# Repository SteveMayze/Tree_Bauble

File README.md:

# Tree_Bauble

## Basic Design
The Tree Bauble is simply a Christmas tree ornament that will contain some blinking LEDs. 
The concept of the design is to take a clear plastic ornament and build into this a main 
board with six arcs of flexible boards that would contain the LEDs.

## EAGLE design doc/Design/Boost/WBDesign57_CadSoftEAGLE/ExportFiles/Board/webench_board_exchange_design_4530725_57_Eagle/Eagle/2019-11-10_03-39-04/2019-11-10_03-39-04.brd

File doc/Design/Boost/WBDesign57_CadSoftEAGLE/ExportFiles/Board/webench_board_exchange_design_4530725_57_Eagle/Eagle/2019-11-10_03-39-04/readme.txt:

**********************************************************
*************  Important Instructions Follow  ************
**********************************************************
 
All files exported to: Z:\\45\\30\\4530725\\57\Eagle\2019-11-10_03-39-04\2019-11-10_03-39-04.xml

**********************************************************
*****************Schematic Instructions  *******************
**********************************************************

To import your new Schematic file into Eagle:

1. Unzip the downloaded folder files to local directory and Start Eagle.
2. Select "File"->"Open"->"Schematic..." from the menu at the top of
the screen.
3. Browse to your newly exported file and select the ".sch" file extension.
4. You should now see your schamtic available in Eagle.

**********************************************************
*******************  PCB Instructions  *******************
**********************************************************

To import your new BOARD file into Eagle:

1. Unzip the downloaded folder files to local directory and Start Eagle.
2. Select "File"->"Open"->"Board..." from the menu at the top of
the screen.
3. Browse to your newly exported file and select the ".brd" file extension.
4. Planes will need to be repoured to update the polygon fills
	1. Once your board is loaded, type "ratsnest" into the command
	   line and press the Enter key.
	2. The polygons should all be filled now.
5. You should now have an image of your board available in Eagle.

**********************************************************
*******************  LIB Instructions  *******************
**********************************************************

To import your new library into Eagle:

1. Start Eagle.
2. Select "File"->"New"->"Library" from the menu.
3. In the blank library window, select "File" -> "Execute Script"
from the menu.
5. Browse to your newly exported Eagle Script file (".scr" file extension)
6. After opening the file, the script will populate the new library.
Layer 93 should NOT exist.
7. Use "File"->Save As: "AcceleratedDesigns_Lib.lbr" and to the desired
location in Eagle native format.
8. Update schematic with the imported library, Select Library and click on Update; open the library file
	and sync. each part.

For additional information, please visit this site:
http://www.accelerated-designs.com/help/Eagle_import.html

You may also find this video helpful:
http://youtu.be/5jGuWY-Yy3Q

**********************************************************
**********************************************************
**********************************************************

Component "C0805C475K8PACTU" renamed to "C0805C475K8PACTU"
Component "C0805C106K8PACTU" renamed to "C0805C106K8PACTU"
Component "GRM21BR71A106KE51L" renamed to "GRM21BR71A106KE51L"
Component "XFL4020-102MEB" renamed to "XFL4020-102MEB"
Component "TPS61022RWUR" renamed to "TPS61022RWUR"
Component "CRCW0402100KFKED" renamed to "CRCW0402100KFKED"
Component "CRCW0402732KFKED" renamed to "CRCW0402732KFKED"
Component "TP-1502" renamed to "TP-1502"

Ultra Librarian Gold 8.1.204 Process Report

Message - Padstack "RX44Y57D0T" Shape(4) is a CIRCLE with no diameter.
Message - Padstack "RX38Y134D0T" Shape(4) is a CIRCLE with no diameter.
Message - Padstack "RX22Y24D0T" Shape(4) is a CIRCLE with no diameter.
Message - Padstack "R10450140000022A" Shape(4) is a CIRCLE with no diameter.
Message - Padstack "R10570080000028A" Shape(4) is a CIRCLE with no diameter.
Message - Padstack "R10180100000000A" Shape(4) is a CIRCLE with no diameter.
Message - Symbol "WB_CAPACITOR" has as multiple attributes named "TYPE".
One of the attributes was renamed to "TYPE_2".
Message - Component "C0805C475K8PACTU" attribute "Cap" references text style "" that is not in the database.
The default pattern text style "H50s3" was substituted.
Message - Component "C0805C475K8PACTU" attribute "ESR" references text style "" that is not in the database.
The default pattern text style "H50s3" was substituted.
Message - Component "C0805C475K8PACTU" attribute "IRMS" references text style "" that is not in the database.
The default pattern text style "H50s3" was substituted.
Message - Component "C0805C475K8PACTU" attribute "VDC" references text style "" that is not in the database.
The default pattern text style "H50s3" was substituted.
Message - Component "C0805C106K8PACTU" attribute "Cap" references text style "" that is not in the database.
The default pattern text style "H50s3" was substituted.
Message - Component "C0805C106K8PACTU" attribute "ESR" references text style "" that is not in the database.
The default pattern text style "H50s3" was substituted.
Message - Component "C0805C106K8PACTU" attribute "IRMS" references text style "" that is not in the database.
The default pattern text style "H50s3" was substituted.
Message - Component "C0805C106K8PACTU" attribute "VDC" references text style "" that is not in the database.
The default pattern text style "H50s3" was substituted.
Message - Component "GRM21BR71A106KE51L" attribute "Cap" references text style "" that is not in the database.
The default pattern text style "H50s3" was substituted.
Message - Component "GRM21BR71A106KE51L" attribute "ESR" references text style "" that is not in the database.
The default pattern text style "H50s3" was substituted.
Message - Component "GRM21BR71A106KE51L" attribute "IRMS" references text style "" that is not in the database.
The default pattern text style "H50s3" was substituted.
Message - Component "GRM21BR71A106KE51L" attribute "VDC" references text style "" that is not in the database.
The default pattern text style "H50s3" was substituted.
Message - Component "XFL4020-102MEB" attribute "L" references text style "" that is not in the database.
The default pattern text style "H50s3" was substituted.
Message - Component "XFL4020-102MEB" attribute "DCR" references text style "" that is not in the database.
The default pattern text style "H50s3" was substituted.
Message - Component "XFL4020-102MEB" attribute "IDC" references text style "" that is not in the database.
The default pattern text style "H50s3" was substituted.
Message - Component "CRCW0402100KFKED" attribute "Resistance" references text style "" that is not in the database.
The default pattern text style "H50s3" was substituted.
Message - Component "CRCW0402100KFKED" attribute "Power" references text style "" that is not in the database.
The default pattern text style "H50s3" was substituted.
Message - Component "CRCW0402100KFKED" attribute "Tolerance" references text style "" that is not in the database.
The default pattern text style "H50s3" was substituted.
Message - Component "CRCW0402732KFKED" attribute "Resistance" references text style "" that is not in the database.
The default pattern text style "H50s3" was substituted.
Message - Component "CRCW0402732KFKED" attribute "Power" references text style "" that is not in the database.
The default pattern text style "H50s3" was substituted.
Message - Component "CRCW0402732KFKED" attribute "Tolerance" references text style "" that is not in the database.
The default pattern text style "H50s3" was substituted.
Message - Pattern "RWU0007A", Attribute "RefDes" is a duplicate Attribute and will be deleted.

TextStyle count:  24
Padstack count:   12
Pattern count:    5
Symbol count:     5
Component count:  8

Export

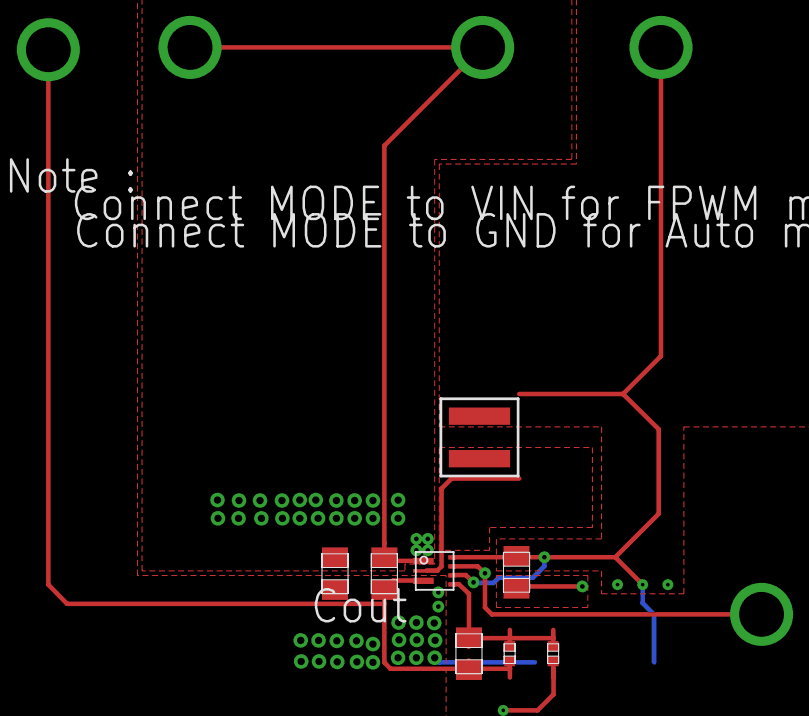
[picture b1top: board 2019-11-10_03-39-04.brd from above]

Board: 4 copper layers, 13 parts (0 on the bottom side), 6 nets.

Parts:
Cff: 0805
Cin: 0805
Cout_1, Cout_2: 0805
GND, GND1: TP-1502
L1: XFL4020
MODE: TP-1502
Rfbb: 0402
Rfbt: 0402
U1: RWU0007A
VIN: TP-1502
VOUT: TP-1502

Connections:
0: Cin.2, Cout_1.2, Cout_2.2, GND.1, GND1.1, Rfbb.2, U1.1
2: Cin.1, L1.1, U1.5, U1.7, VIN.1
3: Cff.2, Rfbb.1, Rfbt.2, U1.4
5: Cff.1, Cout_1.1, Cout_2.1, Rfbt.1, U1.3, VOUT.1
8: MODE.1, U1.6
12: L1.2, U1.2

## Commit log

2019-11-10 README.md added
2019-11-10 Initial Checkin
